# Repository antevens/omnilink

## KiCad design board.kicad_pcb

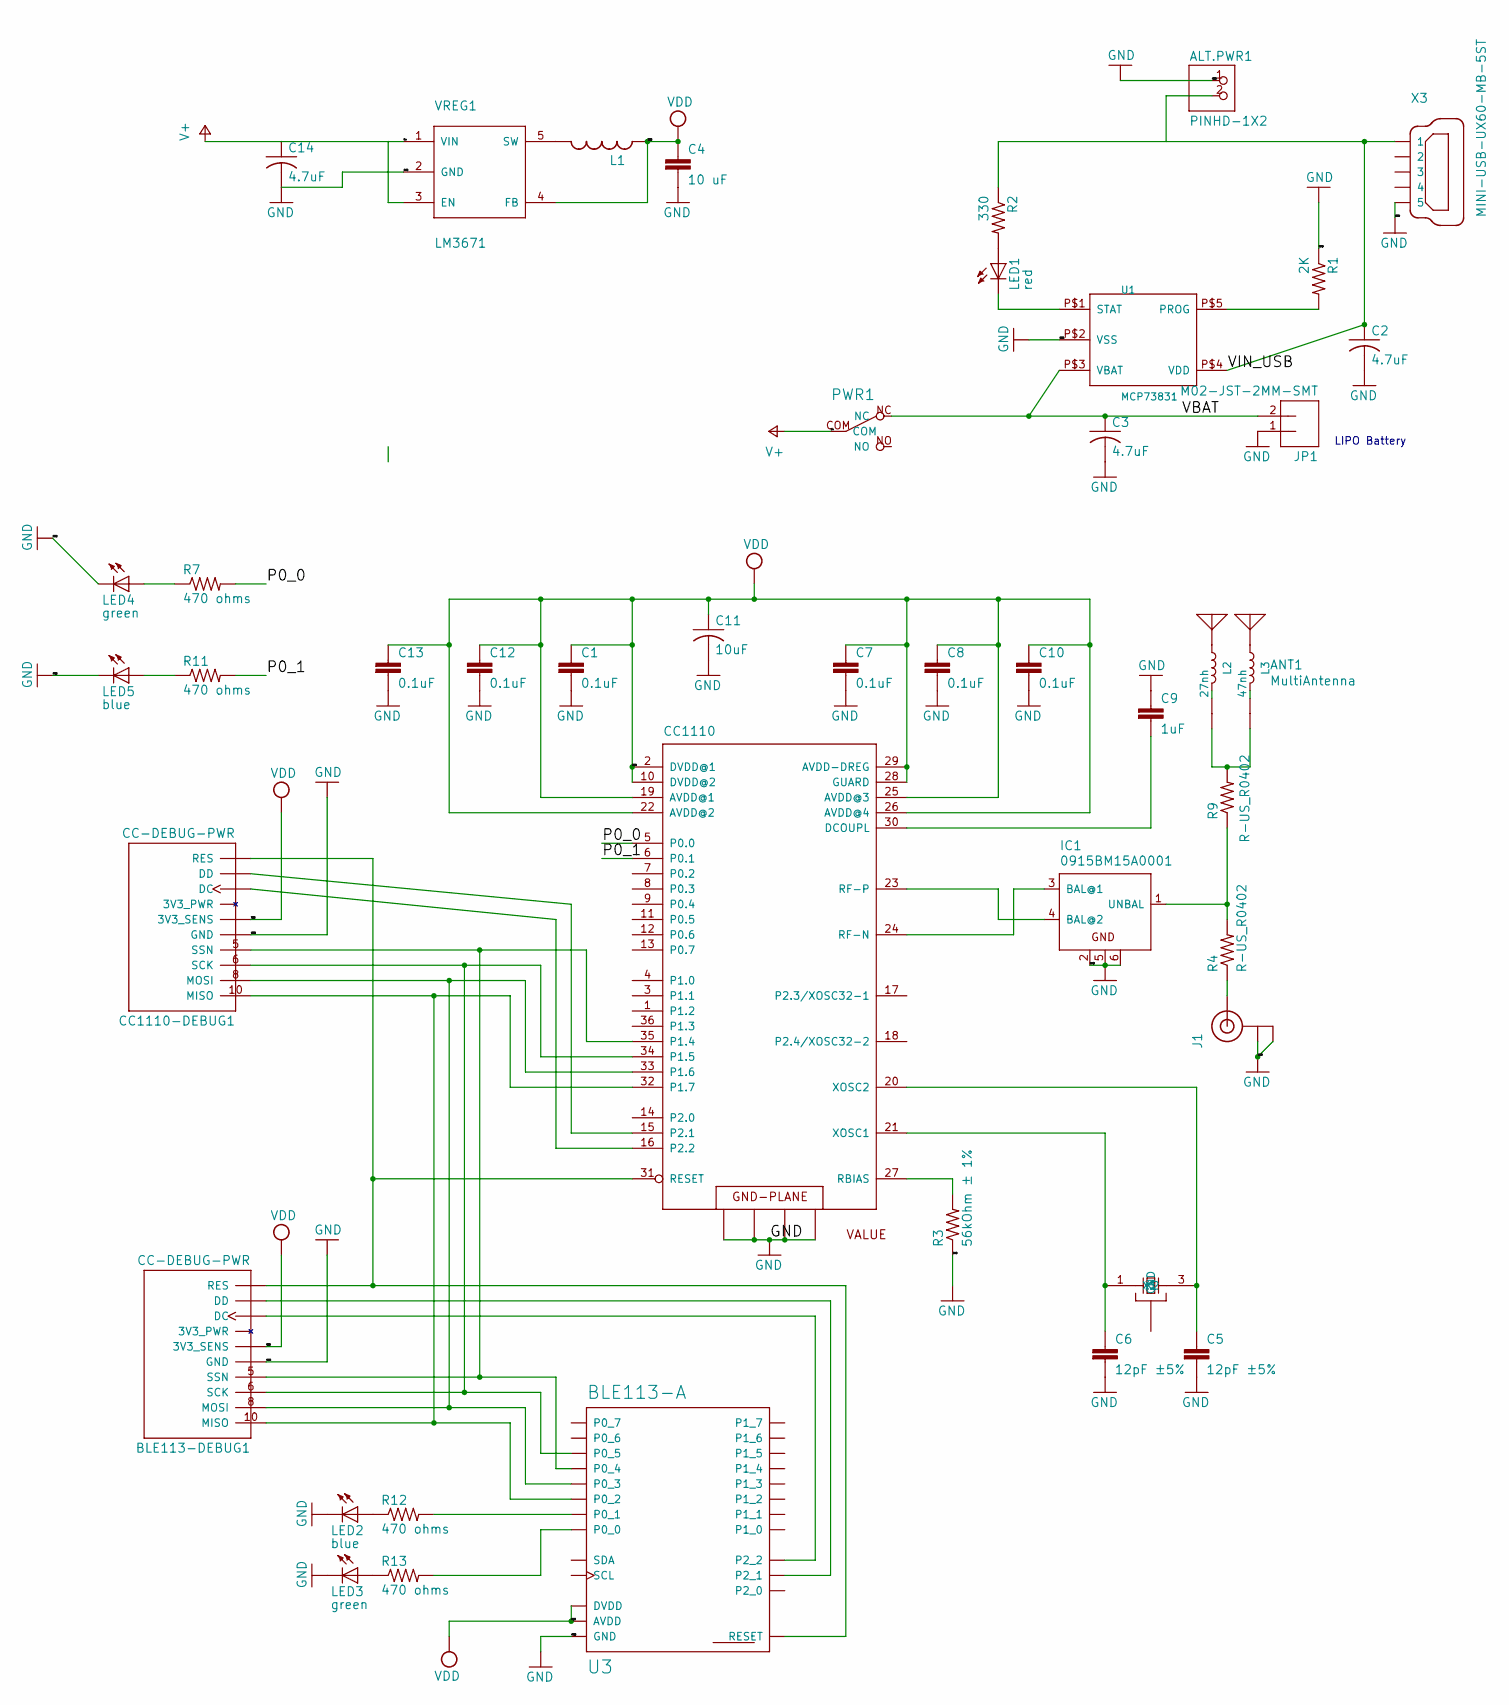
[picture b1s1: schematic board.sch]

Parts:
ALT.PWR1: PINHD-1X2; 1X02
ANT1: MultiAntenna; ComboAntenna
BLE113-DEBUG1: CC-DEBUG-PWR; CC-P05
C1, C7, C8, C10, C12, C13: 0.1uF; C0402
C2, C3, C14: 4.7uF; C0603K
C4: 10 uF; C0805K
C5, C6: 12pF ±5%; C0402K
C9: 1uF; C0402K
C11: 10uF; C0805K
CC1110: CC1110; QLP-36_UPDATE
CC1110-DEBUG1: CC-DEBUG-PWR; CC-P05
IC1: 0915BM15A0001
J1: U.FL
JP1: M02-JST-2MM-SMT; JST-2-SMD
L1: 2.2 uH; L2825P
L2: 27nh; INDC0402X22N
L3: 47nh; INDC0402X22N
LED1: red; SML0603
LED2, LED5: blue; SML0603
LED3, LED4: green; SML0603
PWR1: SW_SLIDE; SLIDE_SWITCH_SMD
R1: 2K; R0402
R2: 330; R0402
R3: 56kOhm ± 1%; R0402
R4, R9: R-US_R0402; R0402
R7, R11, R12, R13: 470 ohms; R0402
U1: MCP73831; 5PIN_SOT23
U3: BLE113-A
VREG1: LM3671; SOT23-5
X1: 24MHz 8pF 10ppm -20C +70C; CTS_32X25
X3: MINI-USB-UX60-MB-5ST; UX60-MB-5ST

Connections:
/P0_0: CC1110.5 (P0.0), R7.2
/P0_1: CC1110.6 (P0.1), R11.2
/VBAT: C3.1, JP1.2 (1), PWR1.NC, U1.P$3 (VBAT)
/VIN_USB: ALT.PWR1.2, C2.1, R2.1, U1.P$4 (VDD), X3.1
GND: ALT.PWR1.1, BLE113-DEBUG1.1 (GND), C1.2, C2.2, C3.2, C4.2, C5.2, C6.2, C7.2, C8.2, C9.1, C10.2, C11.2, C12.2, C13.2, C14.2, CC1110.37 (GND@4), CC1110.38 (GND@3), CC1110.39 (GND@2), CC1110.40 (GND@1), CC1110-DEBUG1.1 (GND), IC1.2 (GND@1), IC1.5 (GND@2), IC1.6 (GND@3), J1.P$1 (GND@0), J1.P$2 (GND@1), JP1.1 (2), LED2.C, LED3.C, LED4.C, LED5.C, R1.1, R3.1, U1.P$2 (VSS), U3.GND, U3.GND@2 (GND), U3.GND@3 (GND), U3.GND@4 (GND), U3.GND@5 (GND), U3.GND@6 (GND), U3.GND@7 (GND), U3.GND@8 (GND), U3.GND@9 (GND), U3.GND@10 (GND), VREG1.2 (GND), X3.5
unnamed: ANT1.1 (433MHz_Antenna), L2.1
unnamed: ANT1.2 (433MHz_ToTuner), L2.2
unnamed: ANT1.3 (433MHz__Untuned), ANT1.6 (915Mhz_Untuned), R9.2
unnamed: ANT1.4 (915Mhz_Antenna), L3.1
unnamed: ANT1.5 (915MHz_ToTuner), L3.2
unnamed: BLE113-DEBUG1.3 (DC), U3.P2_2
unnamed: BLE113-DEBUG1.4 (DD), U3.P2_1
unnamed: BLE113-DEBUG1.5 (SSN), CC1110.35 (P1.4), CC1110-DEBUG1.5 (SSN), U3.P0_4
unnamed: BLE113-DEBUG1.6 (SCK), CC1110.34 (P1.5), CC1110-DEBUG1.6 (SCK), U3.P0_5
unnamed: BLE113-DEBUG1.7 (RES), CC1110.31 (RESET), CC1110-DEBUG1.7 (RES), U3.RESET
unnamed: BLE113-DEBUG1.8 (MOSI), CC1110.33 (P1.6), CC1110-DEBUG1.8 (MOSI), U3.P0_3
unnamed: BLE113-DEBUG1.10 (MISO), CC1110.32 (P1.7), CC1110-DEBUG1.10 (MISO), U3.P0_2
unnamed: C5.1, CC1110.20 (XOSC2), X1.3 (X2)
unnamed: C6.1, CC1110.21 (XOSC1), X1.1 (X1)
unnamed: C9.2, CC1110.30 (DCOUPL)
unnamed: CC1110.16 (P2.2), CC1110-DEBUG1.3 (DC)
unnamed: CC1110.15 (P2.1), CC1110-DEBUG1.4 (DD)
unnamed: CC1110.23 (RF-P), IC1.4 (BAL@2)
unnamed: CC1110.24 (RF-N), IC1.3 (BAL@1)
unnamed: CC1110.27 (RBIAS), R3.2
unnamed: IC1.1 (UNBAL), R4.2, R9.1
unnamed: J1.P$3 (SIGNAL), R4.1
unnamed: L1.2, VREG1.5 (SW)
unnamed: LED1.A, R2.2
unnamed: LED1.C, U1.P$1 (STAT)
unnamed: LED2.A, R12.1
unnamed: LED3.A, R13.1
unnamed: LED4.A, R7.1
unnamed: LED5.A, R11.1
unnamed: R1.2, U1.P$5 (PROG)
unnamed: R12.2, U3.P0_1
unnamed: R13.2, U3.P0_0
unnamed: X1.2 (GND), X1.4 (GND)
V+: C14.1, PWR1.COM, VREG1.1 (VIN), VREG1.3 (EN)
VDD: BLE113-DEBUG1.2 (3V3_SENS), C1.1, C4.1, C7.1, C8.1, C10.1, C11.1, C12.1, C13.1, CC1110.2 (DVDD@1), CC1110.10 (DVDD@2), CC1110.19 (AVDD@1), CC1110.22 (AVDD@2), CC1110.25 (AVDD@3), CC1110.26 (AVDD@4), CC1110.28 (GUARD), CC1110.29 (AVDD-DREG), CC1110-DEBUG1.2 (3V3_SENS), L1.1, U3.AVDD, U3.DVDD, VREG1.4 (FB)

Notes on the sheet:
LIPO Battery

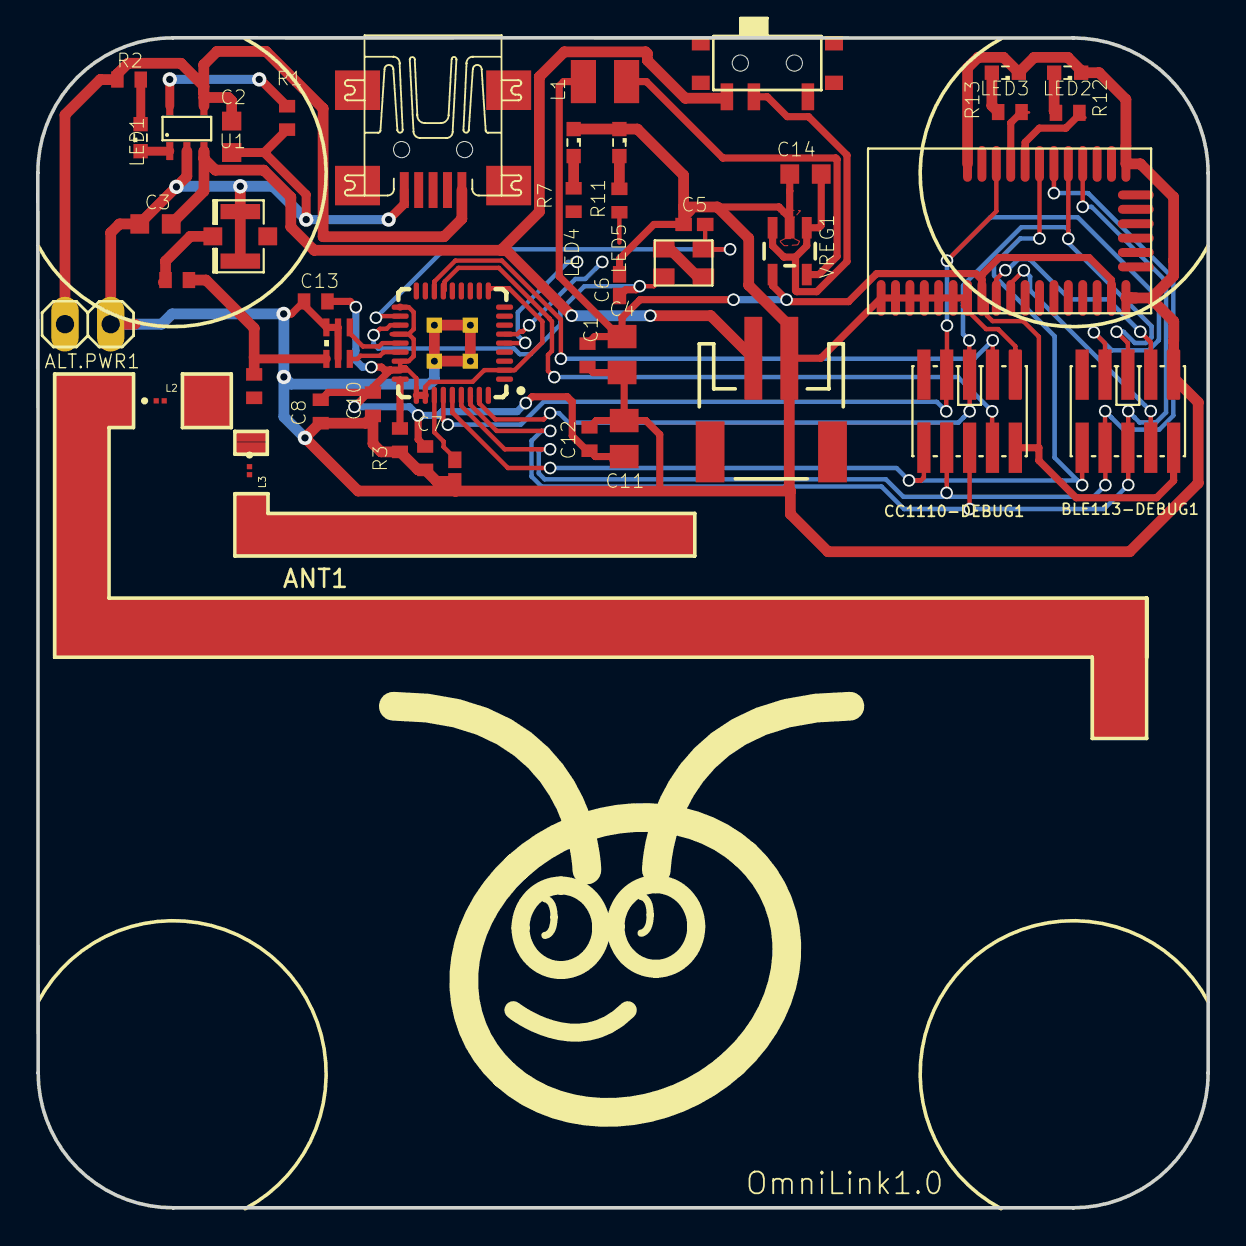
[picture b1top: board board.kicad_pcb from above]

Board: 2 copper layers, 65.0 x 65.0 mm, 45 parts (0 on the bottom side), 40 nets.

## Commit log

2020-03-29 Initial layout
2020-04-10 Fix minor clearance issues

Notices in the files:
parts and their libraries:
Package design from \"pretty-eagle-libs\" at https://github.com/esden/pretty-eagle-libs/blob/master/pel_misc.lbr by @esden at Github. (CC-BY-SA-3.0)
